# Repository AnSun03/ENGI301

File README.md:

# ENGI301
Repository for ENGI301 course work

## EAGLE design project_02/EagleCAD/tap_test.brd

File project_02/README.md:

# Tapping Test PCB 
This PCB design is part of the tapping test project (see project_01). 

## Directories 
### docs
Includes mechanical diagram, published schematic for the PCB, bill of materials, and assembly documents.

### EagleCAD
Includes EagleCAD files for the project, including the library, schematic, and board. To use, download the files and open them in Eagle. Visit http://eagle.autodesk.com/ for more information on the program. 

### mfg 
Manufacturing files, including bill of materials and Gerber files. 

## Disclaimer
The following PCB has not been tested nor verified. Mistakes or unexpected behavior may occur.

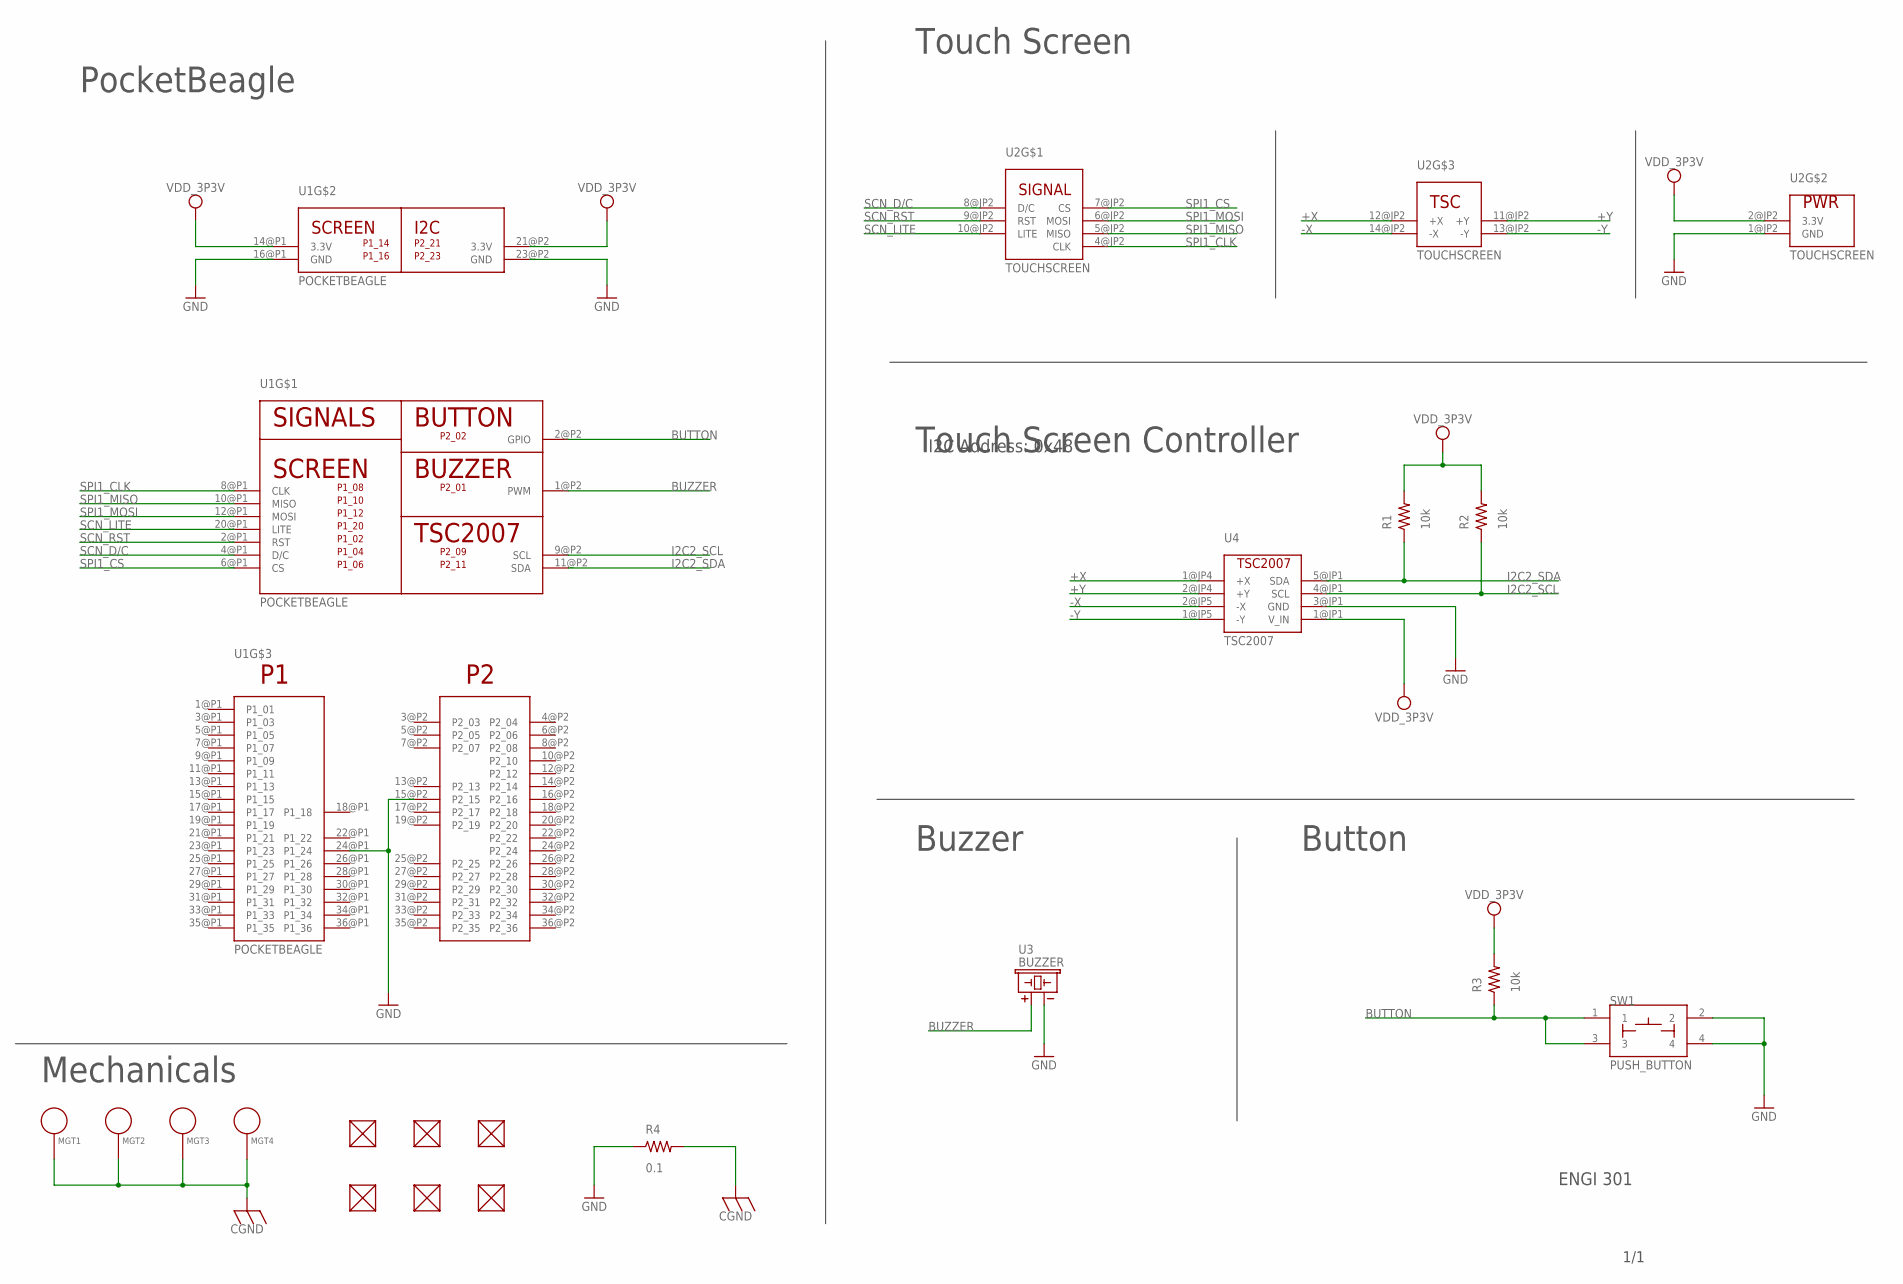
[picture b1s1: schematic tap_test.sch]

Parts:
FUD1, FUD2, FUD3, FUD4, FUD5, FUD6: FIDUCIAL; FIDUCIAL_40MIL
MGT1, MGT2, MGT3, MGT4: MOUNTING_HOLE
R1, R2, R3: 10k; R0603
R4: 0.1; R0603
SW1: PUSH_BUTTON; BUTTON_12.5MM
U1: POCKETBEAGLE
U2: TOUCHSCREEN
U3: BUZZER; BUZZER_6.5MM
U4: TSC2007

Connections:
+X: U2.12@JP2 (+X), U4.1@JP4 (+X)
+Y: U2.11@JP2 (+Y), U4.2@JP4 (+Y)
-X: U2.14@JP2 (-X), U4.2@JP5 (-X)
-Y: U2.13@JP2 (-Y), U4.1@JP5 (-Y)
BUTTON: R3.1, SW1.1, SW1.3, U1.2@P2 (GPIO)
BUZZER: U1.1@P2 (PWM), U3.+
CGND: MGT1.P$1, MGT2.P$1, MGT3.P$1, MGT4.P$1, R4.2
GND: R4.1, SW1.2, SW1.4, U1.15@P2 (P2_15), U1.16@P1 (GND), U1.23@P2 (GND), U1.24@P1 (P1_24), U2.1@JP2 (GND), U3.-, U4.3@JP1 (GND)
I2C2_SCL: R2.1, U1.9@P2 (SCL), U4.4@JP1 (SCL)
I2C2_SDA: R1.1, U1.11@P2 (SDA), U4.5@JP1 (SDA)
SCN_D/C: U1.4@P1 (D/C), U2.8@JP2 (D/C)
SCN_LITE: U1.20@P1 (LITE), U2.10@JP2 (LITE)
SCN_RST: U1.2@P1 (RST), U2.9@JP2 (RST)
SPI1_CLK: U1.8@P1 (CLK), U2.4@JP2 (CLK)
SPI1_CS: U1.6@P1 (CS), U2.7@JP2 (CS)
SPI1_MISO: U1.10@P1 (MISO), U2.5@JP2 (MISO)
SPI1_MOSI: U1.12@P1 (MOSI), U2.6@JP2 (MOSI)
VDD_3P3V: R1.2, R2.2, R3.2, U1.14@P1 (3.3V), U1.21@P2 (3.3V), U2.2@JP2 (3.3V), U4.1@JP1 (V_IN)

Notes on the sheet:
PocketBeagle
I2C Address: 0x48
Touch Screen Controller
Buzzer
Button
Touch Screen
Mechanicals
ENGI 301
1/1

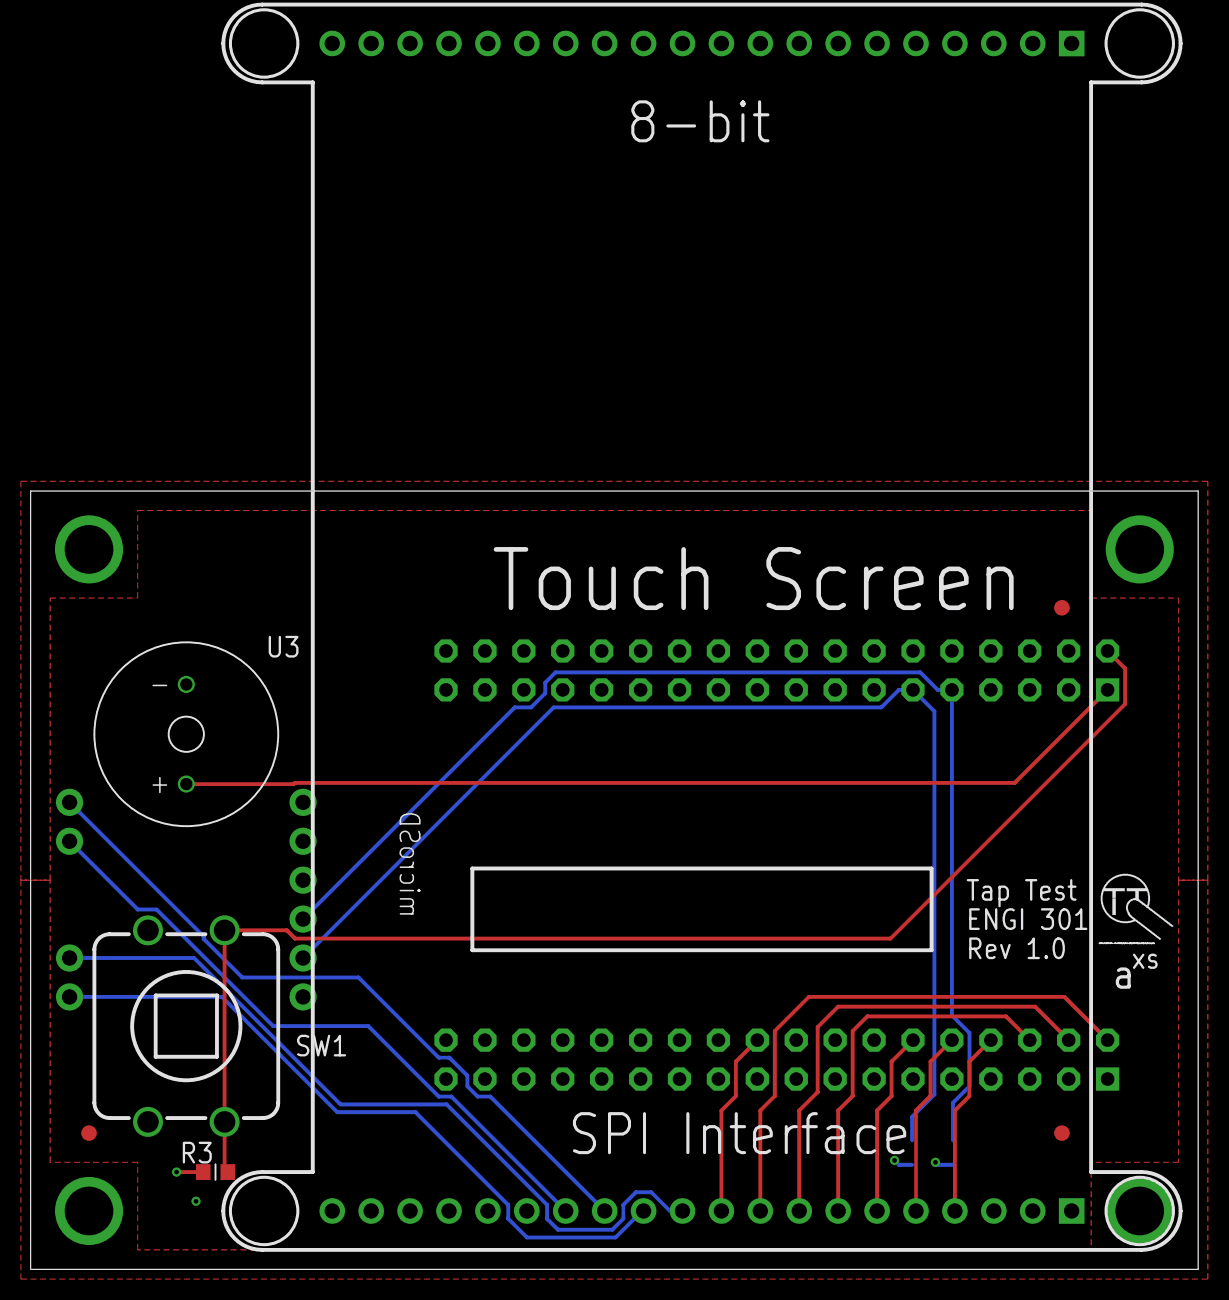
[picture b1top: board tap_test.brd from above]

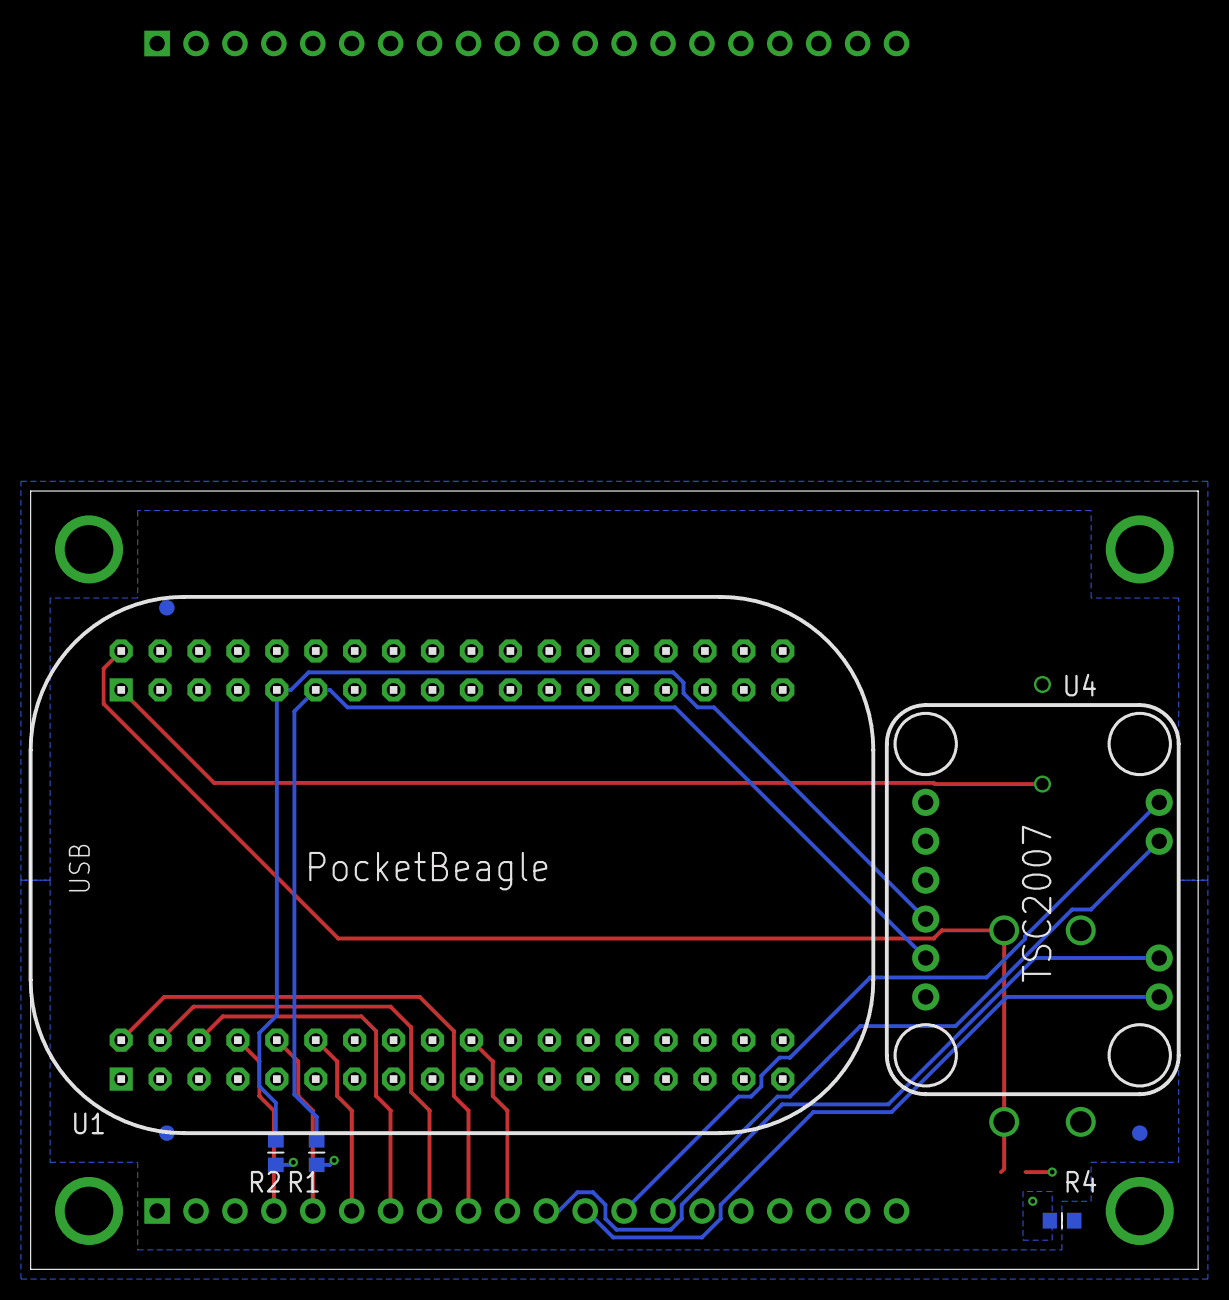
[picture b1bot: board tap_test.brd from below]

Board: 4 copper layers, 76.2 x 50.8 mm, 19 parts (8 on the bottom side), 18 nets.

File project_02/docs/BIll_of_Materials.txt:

Partlist exported from C:/Users/waywi/OneDrive - Rice University/Documents/EAGLE/libraries/tap_test.sch at 4/29/2023 5:23 AM

Qty Value         Device        Package        Parts                              Description                                    
1   0.1           R_R0603       R0603          R4                                 RESISTOR, American symbol                      
3   10k           R_R0603       R0603          R1, R2, R3                         RESISTOR, American symbol                      
1   BUZZER        BUZZER        BUZZER_6.5MM   U3                                 CEM-1203 Buzzer                                
6   FIDUCIAL      FIDUCIAL      FIDUCIAL_40MIL FUD1, FUD2, FUD3, FUD4, FUD5, FUD6                                                
4   MOUNTING_HOLE MOUNTING_HOLE MOUNTING_HOLE  MGT1, MGT2, MGT3, MGT4             Chassis Mounting Hole w/GND connection ability 
1   POCKETBEAGLE  POCKETBEAGLE  POCKETBEAGLE   U1                                                                                
1   PUSH_BUTTON   PUSH_BUTTON   BUTTON_12.5MM  SW1                                                                               
1   TOUCHSCREEN   TOUCHSCREEN   TOUCHSCREEN    U2                                 ILI9341, Adafruit 2.8" TFT LCD, Resistive touch screen                                               
1   TSC2007       TSC2007       TSC2007        U4                                 TSC2007, Adafruit resistive touch screen controller

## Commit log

2023-02-14 adding new file
2023-02-14 Moving file
2023-02-14 add blink USR3
2023-02-15 Add button
2023-02-19 Created new file
2023-03-07 System and software block diagrams.
2023-03-16 example project
2023-03-16 mixed combo_lock
2023-03-22 Framework for tapping test
2023-03-22 Tapping_test first version
2023-03-26 completed display driver
2023-03-26 finished display driver
2023-03-26 added touch screen driver
2023-03-30 added basic game framework
2023-03-30 added buzzer game
2023-03-31 add speed test
2023-04-04 documentation
2023-04-04 corrected documentation
2023-04-30 added PCB files
